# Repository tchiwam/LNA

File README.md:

# LNA

Lowest NF possible on PCB for about 30dB gain
Works at -40C

QPL90?? under review

# Power supply
Works at -40C
lowest possible noise rejection
lowest DC ripple

4x LT3045  in progress 

CC license coming soon..

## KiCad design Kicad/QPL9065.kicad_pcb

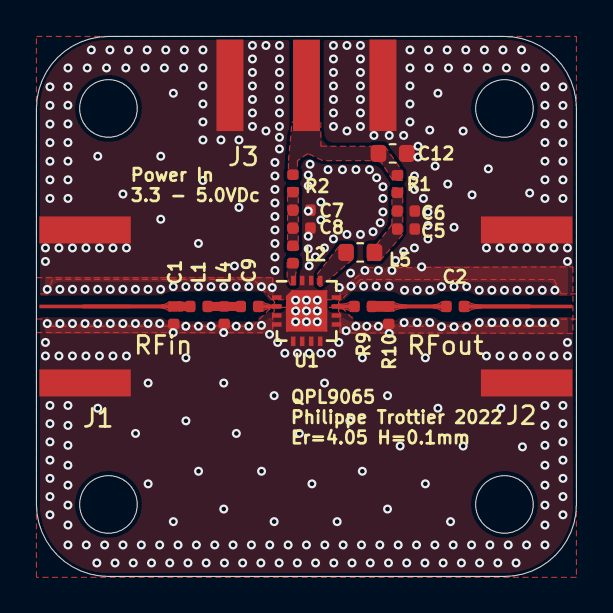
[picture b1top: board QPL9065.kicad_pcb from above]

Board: 4 copper layers, 30.0 x 30.0 mm, 24 parts (0 on the bottom side), 12 nets.

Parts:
C1: 0.5pF; C_0402_1005Metric
C2, C5, C7: 100pF; C_0402_1005Metric
C6, C8: 0.1µF; C_0402_1005Metric
C9: 10pF; C_0402_1005Metric
C12: 4.7µF; C_0603_1608Metric
J1, J2: Conn_Coaxial; ‎142-1701-626‎
J3: Conn_Coaxial_Power; 132147-48
L1: 1.5nH; L_0402_1005Metric
L2: 2.2nH; L_0402_1005Metric
L4: 6.8nH; L_0402_1005Metric
L5: 18nH; L_0603_1608Metric
MH1, MH2, MH3, MH4: MountingHole_Pad; MountingHole_3.2mm_M3
R1, R2: 0; R_0402_1005Metric
R9: 5.1; R_0402_1005Metric
R10: 39k; R_0402_1005Metric
U1: QPL9065; UQFN-16-1EP_3x3mm_P0.5mm_QPL9065

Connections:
/RFin: C1.2, J1.1 (In), L1.2
/RFout: C2.2, J2.1 (In)
GND: C1.1, C5.2, C6.2, C7.2, C8.2, C12.2, J1.2 (Ext), J2.2 (Ext), J3.2 (Ext), L4.2, R10.1, U1.1 (GND), U1.3 (GND), U1.4 (GND), U1.5 (VPD1), U1.6 (VPD2), U1.7 (GND), U1.8 (Vbyp), U1.9 (GND), U1.10 (GND), U1.12 (GND), U1.14 (GND), U1.15 (GND), U1.17 (GND)
unnamed: C2.1, R9.1, R10.2
unnamed: C5.1, C6.1, L5.2, R1.1
unnamed: C7.1, C8.1, L2.2, R2.2
unnamed: C9.1, L1.1, L4.1
unnamed: C9.2, U1.2 (RF_in)
unnamed: L2.1, U1.16 (VDD1)
unnamed: L5.1, U1.13 (VDD2)
unnamed: R9.2, U1.11 (RF_out)
VDC: C12.1, J3.1 (In), R1.2, R2.1

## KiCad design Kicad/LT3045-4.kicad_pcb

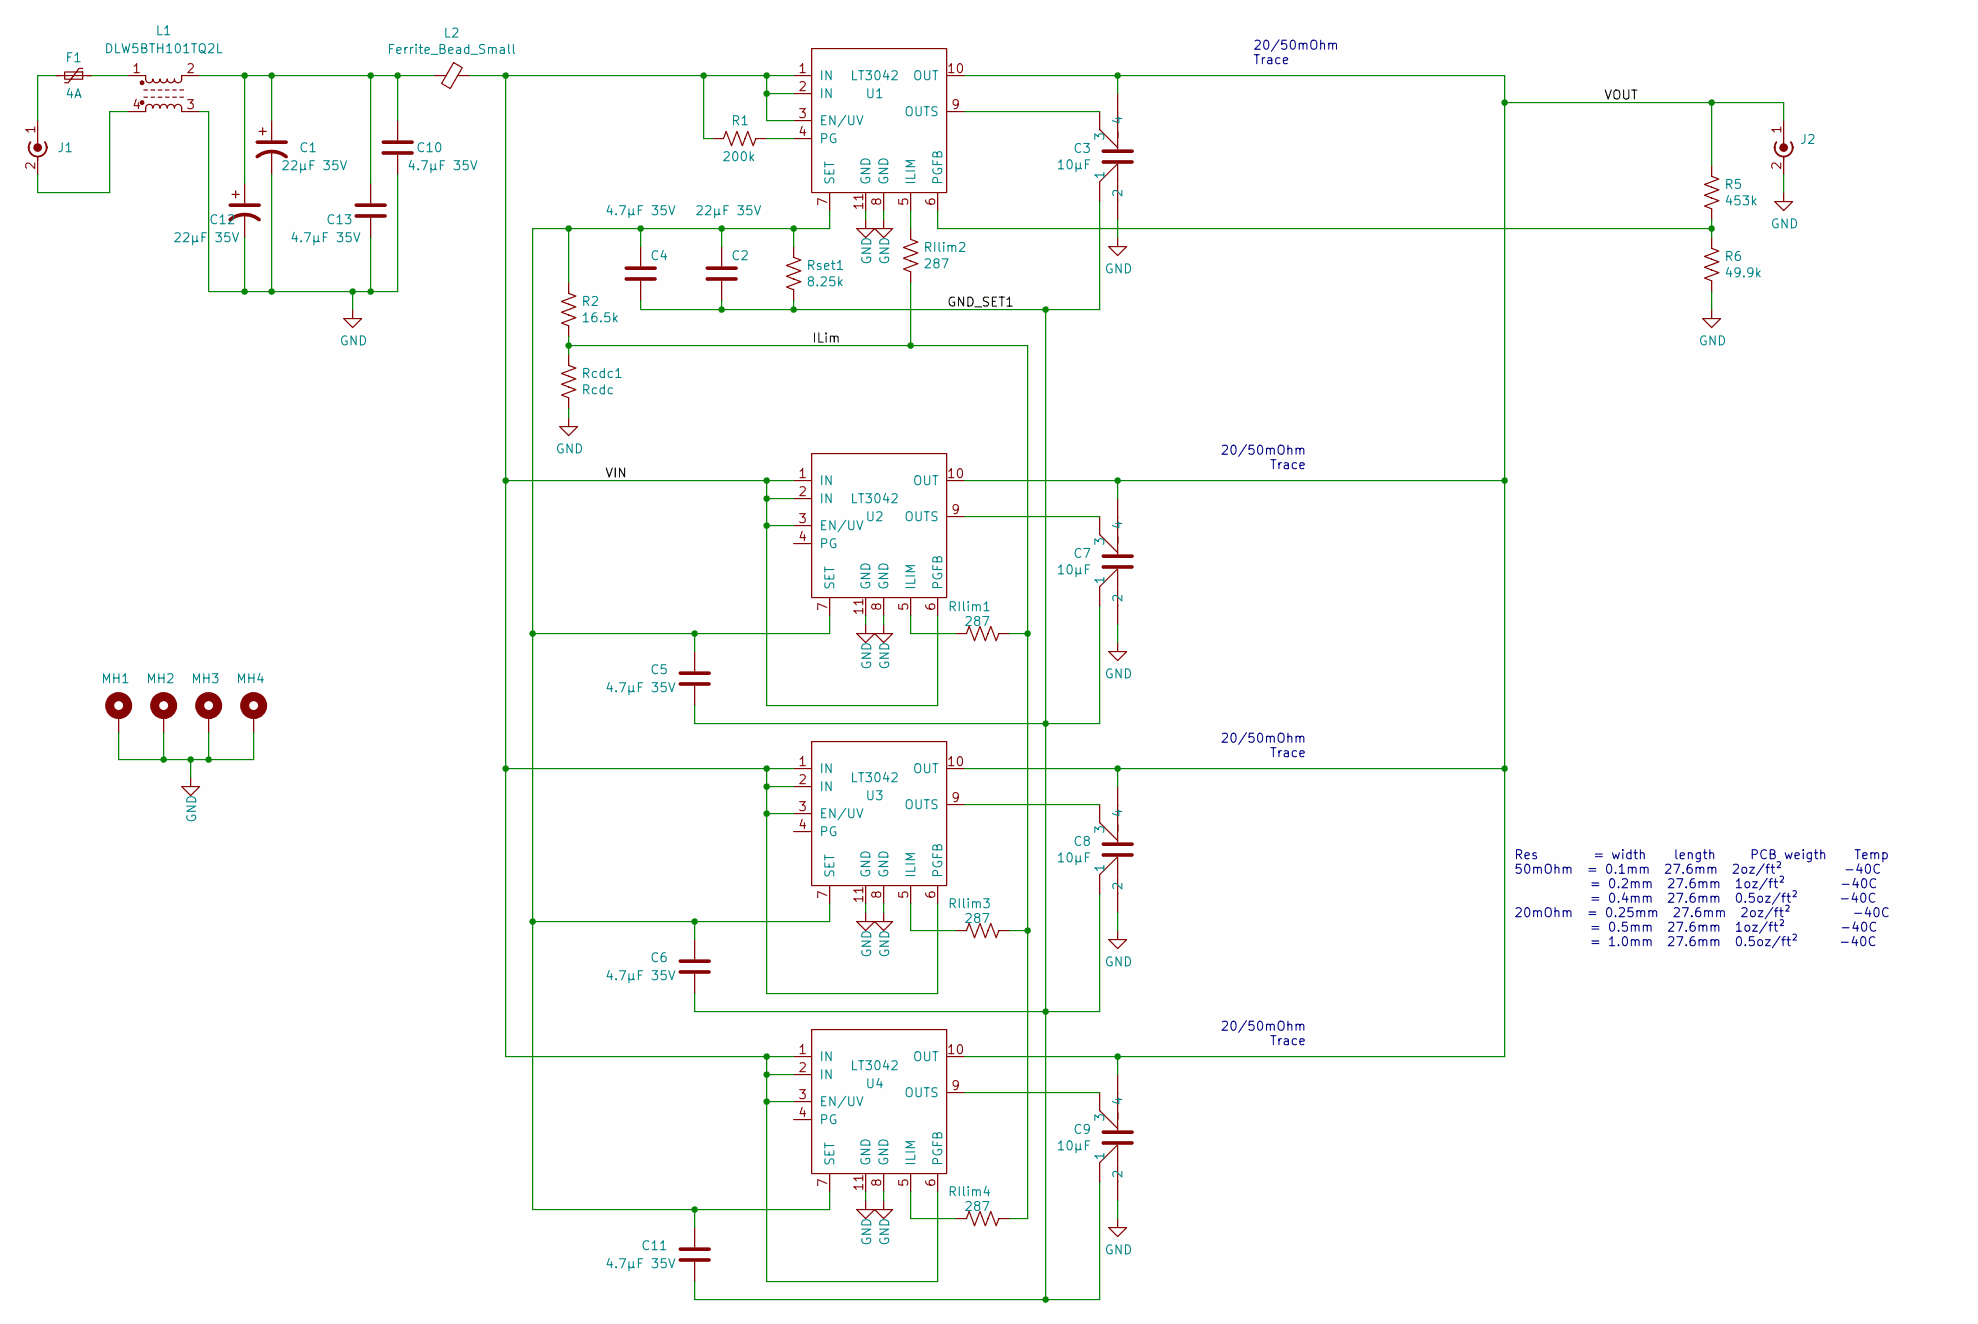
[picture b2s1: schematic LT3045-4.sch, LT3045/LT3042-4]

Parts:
C1, C12: 22µF 35V; CP_EIA-7343-30_AVX-N
C2: 22µF 35V; C_2220_5650Metric
C3, C7, C8, C9: 10µF; C_1206_3216Metric_SPLIT
C4, C5, C6, C10, C11, C13: 4.7µF 35V; C_0805_2012Metric
F1: 4A; Fuse_Bourns_MF-SM_9.5x6.71mm
J1, J2: Conn_Coaxial_Power; SMA_Amphenol_132289_EdgeMount
L1: DLW5BTH101TQ2L; CMC_DLW5BTH
L2: Ferrite_Bead_Small; L_1206_3216Metric
MH1, MH2, MH3, MH4: MountingHole_Pad; MountingHole_3.2mm_M3
R1: 200k; R_0603_1608Metric
R2: 16.5k; R_0603_1608Metric
R5: 453k; R_0603_1608Metric
R6: 49.9k; R_0603_1608Metric
RIlim1, RIlim2, RIlim3, RIlim4: 287; R_0603_1608Metric
Rcdc1: Rcdc; R_0603_1608Metric
Rset1: 8.25k; R_0603_1608Metric
U1, U2, U3, U4: LT3042; DFN-10-1EP_3x3mm_P0.5mm_EP1.65x2.38mm

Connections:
/GND_SET1: C2.2, C3.1, C4.2, C5.2, C6.2, C7.1, C8.1, C9.1, C11.2, Rset1.2
/ILim: R2.2, RIlim1.2, RIlim2.2, RIlim3.2, RIlim4.2, Rcdc1.1
/VIN: L2.1, R1.2, U1.1 (IN), U1.2 (IN), U1.3 (EN/UV), U2.1 (IN), U2.2 (IN), U2.3 (EN/UV), U2.6 (PGFB), U3.1 (IN), U3.2 (IN), U3.3 (EN/UV), U3.6 (PGFB), U4.1 (IN), U4.2 (IN), U4.3 (EN/UV), U4.6 (PGFB)
/VOUT: C3.4, C7.4, C8.4, C9.4, J2.1 (In), R5.1, U1.10 (OUT), U2.10 (OUT), U3.10 (OUT), U4.10 (OUT)
GND: C1.2, C3.2, C7.2, C8.2, C9.2, C10.2, C12.2, C13.2, J2.2 (Ext), L1.3, MH1.1, MH2.1, MH3.1, MH4.1, R6.2, Rcdc1.2, U1.8 (GND), U1.11 (GND), U2.8 (GND), U2.11 (GND), U3.8 (GND), U3.11 (GND), U4.8 (GND), U4.11 (GND)
unnamed: C1.1, C10.1, C12.1, C13.1, L1.2, L2.2
unnamed: C3.3, U1.9 (OUTS)
unnamed: C7.3, U2.9 (OUTS)
unnamed: C8.3, U3.9 (OUTS)
unnamed: C9.3, U4.9 (OUTS)
unnamed: C2.1, C4.1, C5.1, C6.1, C11.1, R2.1, Rset1.1, U1.7 (SET), U2.7 (SET), U3.7 (SET), U4.7 (SET)
unnamed: F1.1, L1.1
unnamed: F1.2, J1.1 (In)
unnamed: J1.2 (Ext), L1.4
unnamed: R1.1, U1.4 (PG)
unnamed: R5.2, R6.1, U1.6 (PGFB)
unnamed: RIlim1.1, U2.5 (ILIM)
unnamed: RIlim2.1, U1.5 (ILIM)
unnamed: RIlim3.1, U3.5 (ILIM)
unnamed: RIlim4.1, U4.5 (ILIM)

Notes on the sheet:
20/50mOhm Trace
Res = width length PCB weigth Temp 50mOhm = 0.1mm 27.6mm 2oz/ft² -40C = 0.2mm 27.6mm 1oz/ft² -40C = 0.4mm 27.6mm 0.5oz/ft² -40C 20mOhm = 0.25mm 27.6mm 2oz/ft² -40C = 0.5mm 27.6mm 1oz/ft² -40C = 1.0mm 27.6mm 0.5oz/ft² -40C

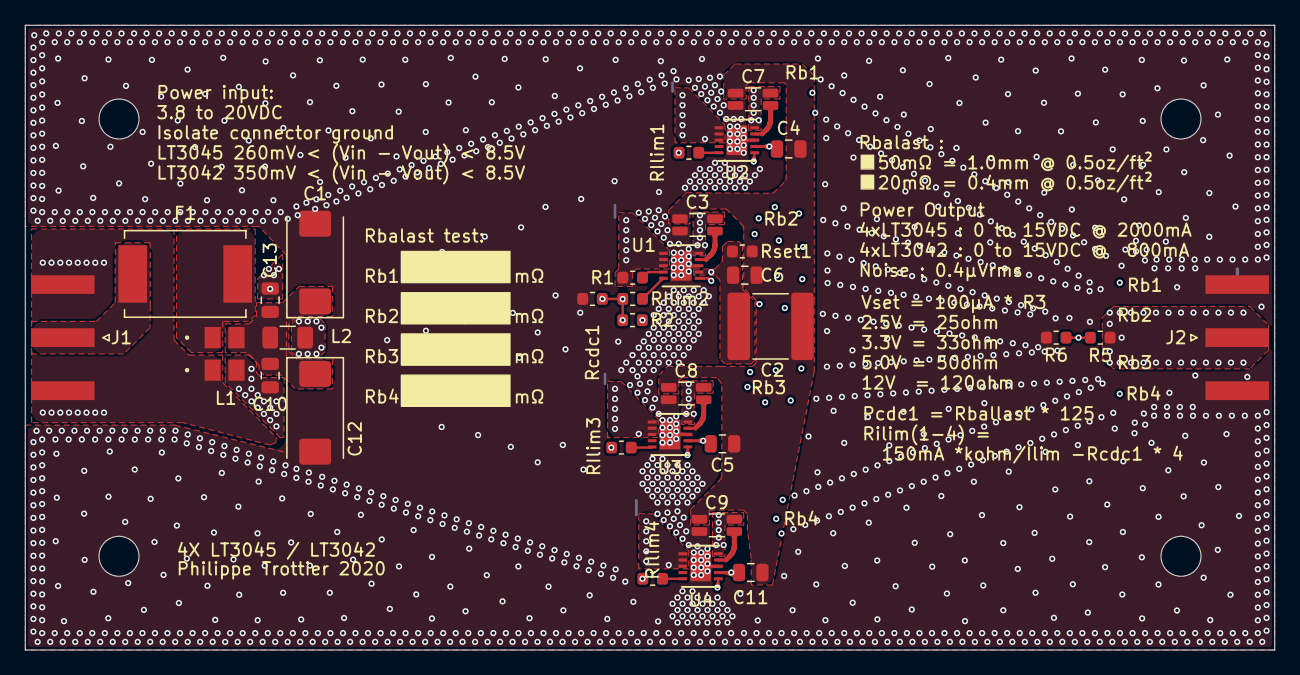
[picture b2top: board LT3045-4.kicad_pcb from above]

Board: 4 copper layers, 100.0 x 50.0 mm, 36 parts (0 on the bottom side), 20 nets.

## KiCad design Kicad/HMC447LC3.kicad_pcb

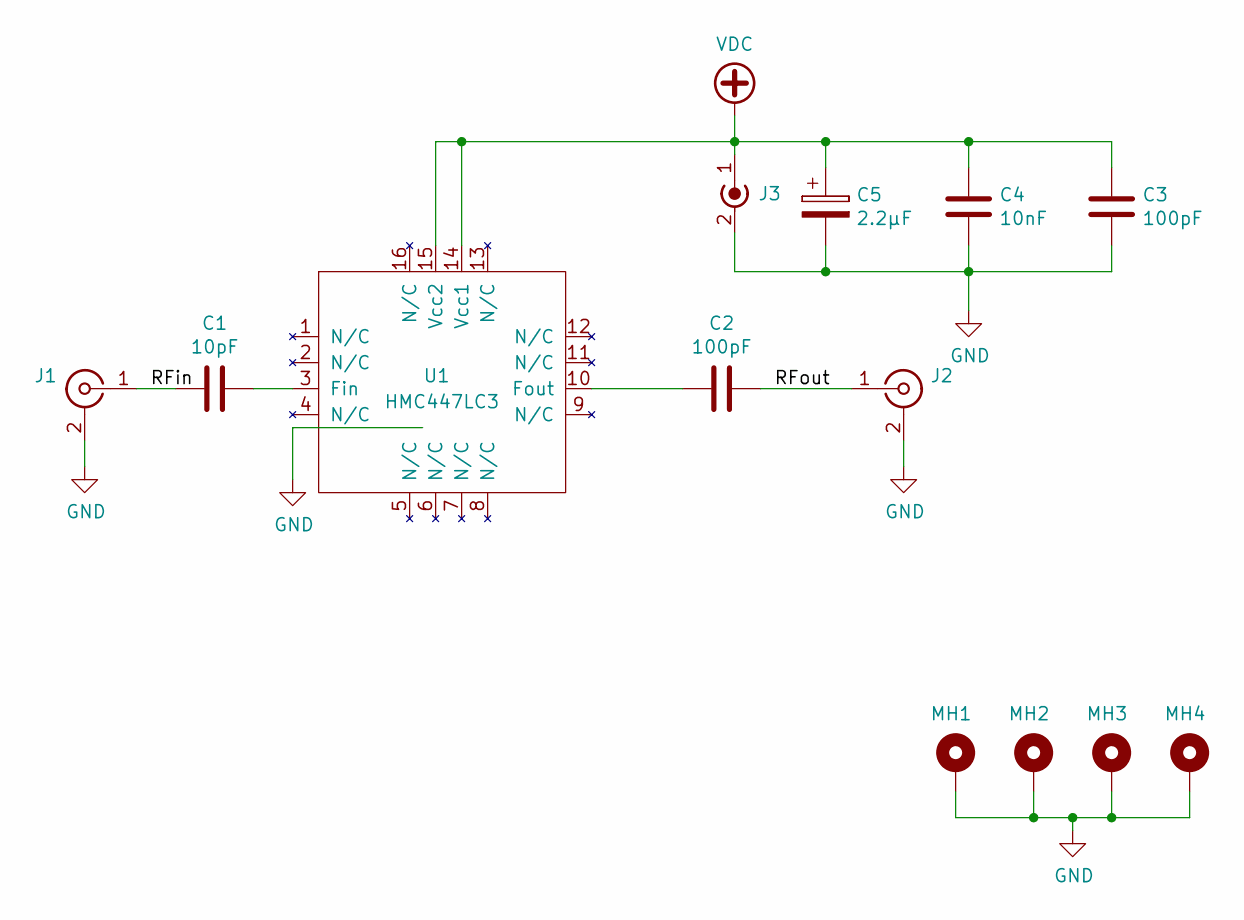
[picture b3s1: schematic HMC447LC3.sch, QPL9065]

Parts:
C1: 10pF; C_0402_1005Metric
C2, C3: 100pF; C_0402_1005Metric
C4: 10nF; C_0603_1608Metric
C5: 2.2µF; C_1206_3216Metric
J1, J2: Conn_Coaxial; SMA_Amphenol_132289_EdgeMount-RF
J3: Conn_Coaxial_Power; SMA_Amphenol_132289_EdgeMount-RF
MH1, MH2, MH3, MH4: MountingHole_Pad; MountingHole_3.2mm_M3
U1: HMC447LC3; UQFN-16-1EP_3x3mm_P0.5mm_HMC447LC3

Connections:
/RFin: C1.1, J1.1 (In)
/RFout: C2.2, J2.1 (In)
GND: C3.2, C4.2, C5.2, J1.2 (Ext), J2.2 (Ext), J3.2 (Ext), MH1.1, MH2.1, MH3.1, MH4.1, U1.17 (GND)
unnamed: C1.2, U1.3 (Fin)
unnamed: C2.1, U1.10 (Fout)
VDC: C3.1, C4.1, C5.1, J3.1 (In), U1.14 (Vcc1), U1.15 (Vcc2)

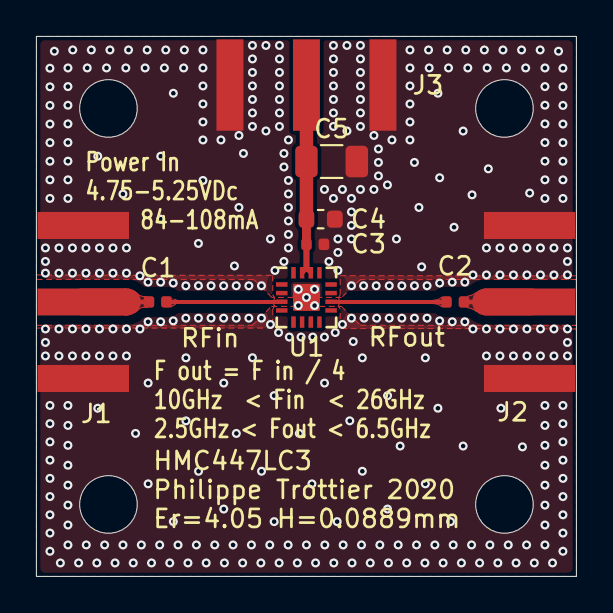
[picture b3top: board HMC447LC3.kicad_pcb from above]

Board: 4 copper layers, 30.0 x 30.0 mm, 13 parts (0 on the bottom side), 6 nets.

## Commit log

2020-11-10 initial design
2020-11-10 1st design
2020-11-10 1st draft
2020-11-10 Passed DRC minux pad to pad clearance
2020-11-10 Pictures and gerber
2020-12-12 VIAS
2020-12-13 letters and little fixes
2020-12-13 Gerber and pdf update
2020-12-13 Input ground fix, added drill files
2020-12-14 Lost revision :(
2020-12-14 And another try
2020-12-14 clean up
2020-12-14 removed orphaned ground pour
2020-12-14 Added bar board
2020-12-14 line width mistake corrected on silk screen
2020-12-15 1st LNA
2020-12-15 schematic pdf added
2020-12-15 Shield line, new footprint, cleanup
2020-12-15 new schematic
2020-12-15 added bare board jpg
2020-12-16 divide by 4 test unit
2021-01-21 Case, Impedence matchine LNA
2022-07-25 QPL rework
2022-07-25 Clean up new pictures
